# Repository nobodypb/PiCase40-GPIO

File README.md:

# PiCase40-GPIO

Fixing the GPIO rows order of Cooler Masters Pi Case 40.
KiCAD project for custom header pcb in `PiHeader`.

**NOT FULLY TESTED YET!**

## Guide for fixing with custom made ribbon cable

This is intended as fix **instead** of a custom PCB, so please don't try to combine both.

Overall you *only* need to get two things and stick them together:

On the top you see basically a plain female to female ribbon cable. Such are also often used for the RasPi T-Cobbler.
This specific version I've made myself to arrange the connectors on opposite sides and make it as short as possible, but a longer cable with connectors on the same side will also work.
Just note that the notch on the connector must be facing upwards when it is plugged into the Case40 for it to fit. So get a cable with one notch faced like below.

The second part you need is a male to male pinheader with (equally) **long pins on both sides**. Those pins should be at least 5.7mm in length on both sides. Spacing is 2.54mm and ofcourse you need 2x20 pins.
That sounds pretty simple, but as I discovered, it's hard to find and get. If you find distributors for this, please tell me.

A list of possible sources:
* [Aliexpress](https://www.aliexpress.com/item/33021895185.html)
* [Digikey](https://www.digikey.com/product-detail/en/sullins-connector-solutions/PRPC020DABN-RC/S2021EC-20-ND/2775919)
* [Kenable](https://www.kenable.co.uk/en/computer-cables-peripherals/ide-cables/1250-ide-pata-40-pin-40pin-coupler-adapter-male-pins-to-male-pins-001250-5055383412501.html) (also sells on amazon)
* [Schmartboard](https://schmartboard.com/qty-4-2-x-20-male-extra-long-headers-920-0198-01/)

If you fail to get one of those, try your luck on using two single row headers. Like these: [Aliexpress](https://www.aliexpress.com/item/32651418137.html)

After you managed to get those two parts you simply stick them together and one end into the header of your Pi Case40:

Afterwards you can use yours HATs aus usual! Just make sure not to plug in the HAT the wrong way around, especially if your plugs are facing the same direction.

## Quick evening update

I've recieved my ordered PCBs today and wanted to share a quick update:

As you can see the physical dimensions of the PCB are all correct and fit really well.

The pin header also is correct, but due to the missing spacing aligned to the bottom of the opening.
I've already successfully tested a small hack to add some spacing that worked very well and got the header to the center.
That is only applicable when assembling by hand though.

The button has a small offset to the right, that's something I'll fix in the layout soon. While this isn't affecting functionality there is another problem that does.
Without TPU the button works just fine, but otherwise it's to short to get pressed. That's because I didn't find one with 10.5mm in height, but used 9.6mm. Therefore here is also a spacing hack needed.
Besides that the operation force of the button I used seems to be to low. With TPU I barely get haptic feedback when pressing it. I've used `TL1105GF160Q` so I suggest to try `TL1105GF250Q` or something with an equally high actuation force.

I've soldered one version together and tried the fitting of the RasPi. In X and Y direction, there's no problem. The pin headers fit like a charm and even are easier to pull out then the original due to lower height.
Since I ordered a board with a thickness of 1.6mm for the first test, I still had to test if the cooler was in contact with the SoC. For this I used some plasticine.

As expected, the gap is a bit higher than with the original board, but even with just one thermal pad it might still work. 
To be on the safe side, I used two pads and with those I clearly felt the back pressure. On the left side, I couldn't even tighten the screws strongly to avoid bending the board.

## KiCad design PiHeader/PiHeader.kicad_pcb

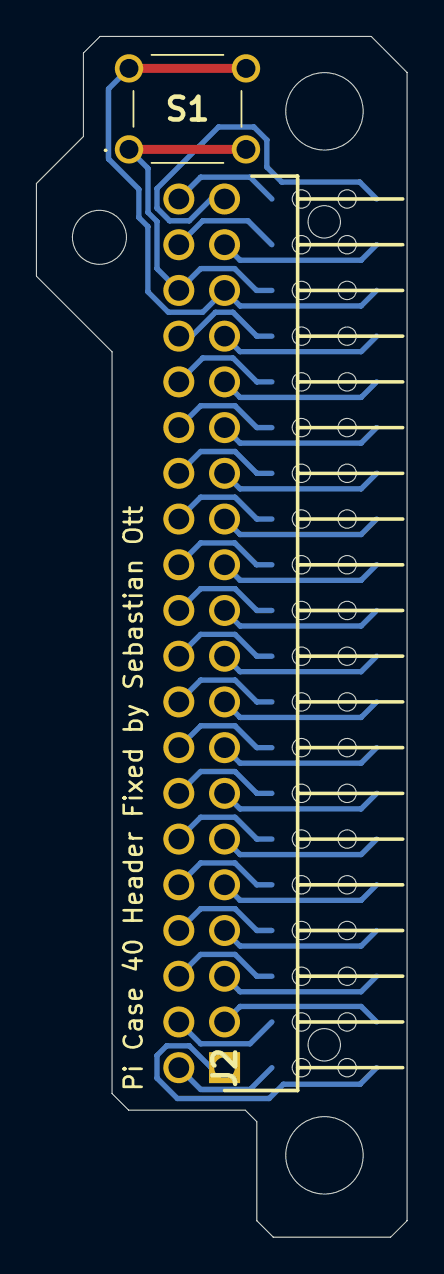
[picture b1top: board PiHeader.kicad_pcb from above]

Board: 2 copper layers, 20.6 x 66.7 mm, 3 parts (1 on the bottom side), 40 nets.

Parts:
J1: M20-7812045; M207812045
J2: 10129382-940001BLF; HDRRA40W67P254_2X20_5080X254X508P
S1: TL1105GF160Q

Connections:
/P1: J1.2, J2.40
/P2: J1.1, J2.39
/P3: J1.4, J2.38
/P4: J1.3, J2.37
/P5: J1.6, J2.36, S1.1, S1.2
/P6: J1.5, J2.35, S1.3, S1.4
/P7: J1.8, J2.34
/P8: J1.7, J2.33
/P9: J1.10, J2.32
/P10: J1.9, J2.31
/P11: J1.12, J2.30
/P12: J1.11, J2.29
/P13: J1.14, J2.28
/P14: J1.13, J2.27
/P15: J1.16, J2.26
/P16: J1.15, J2.25
/P17: J1.18, J2.24
/P18: J1.17, J2.23
/P19: J1.20, J2.22
/P20: J1.19, J2.21
/P21: J1.22, J2.20
/P22: J1.21, J2.19
/P23: J1.24, J2.18
/P24: J1.23, J2.17
/P25: J1.26, J2.16
/P26: J1.25, J2.15
/P27: J1.28, J2.14
/P28: J1.27, J2.13
/P29: J1.30, J2.12
/P30: J1.29, J2.11
/P31: J1.32, J2.10
/P32: J1.31, J2.9
/P33: J1.34, J2.8
/P34: J1.33, J2.7
/P35: J1.36, J2.6
/P36: J1.35, J2.5
/P37: J1.38, J2.4
/P38: J1.37, J2.3
/P39: J1.40, J2.2
/P40: J1.39, J2.1

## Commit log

2021-01-05 Added KiCAD project
2021-01-05 Added datasheets
2021-01-05 Included parts library with 3dmodels
2021-01-10 Recieved PCBs. Quick Update
2021-01-15 Added fix with custom ribbon cable
